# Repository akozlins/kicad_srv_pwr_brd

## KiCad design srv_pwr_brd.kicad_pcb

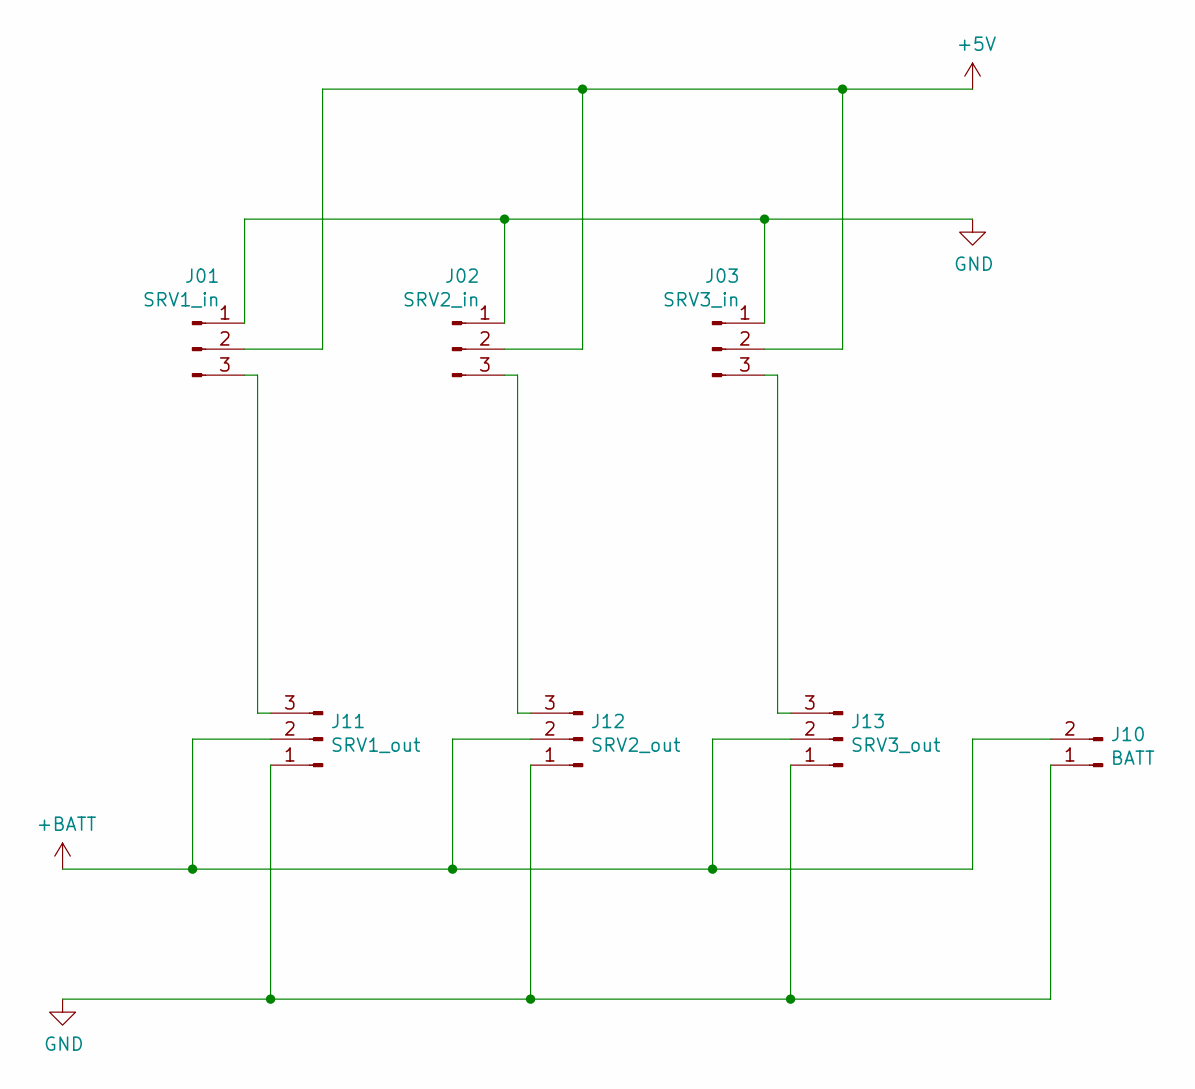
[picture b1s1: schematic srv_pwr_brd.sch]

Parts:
J01: SRV1_in; PinHeader_1x03_P2.54mm_Vertical
J02: SRV2_in; PinHeader_1x03_P2.54mm_Vertical
J03: SRV3_in; PinHeader_1x03_P2.54mm_Vertical
J10: BATT; PinHeader_1x02_P2.54mm_Vertical
J11: SRV1_out; PinHeader_1x03_P2.54mm_Vertical
J12: SRV2_out; PinHeader_1x03_P2.54mm_Vertical
J13: SRV3_out; PinHeader_1x03_P2.54mm_Vertical

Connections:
+5V: J01.2, J02.2, J03.2
+BATT: J10.2, J11.2, J12.2, J13.2
GND: J01.1, J02.1, J03.1, J10.1, J11.1, J12.1, J13.1
unnamed: J01.3, J11.3
unnamed: J02.3, J12.3
unnamed: J03.3, J13.3

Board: 2 copper layers, 7 parts (0 on the bottom side), 6 nets, no tracks yet.

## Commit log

2021-04-01 init
2021-04-01 start kicad proj
2021-04-01 first schematic
2021-06-02 add BATT header
2021-06-02 start pcb
